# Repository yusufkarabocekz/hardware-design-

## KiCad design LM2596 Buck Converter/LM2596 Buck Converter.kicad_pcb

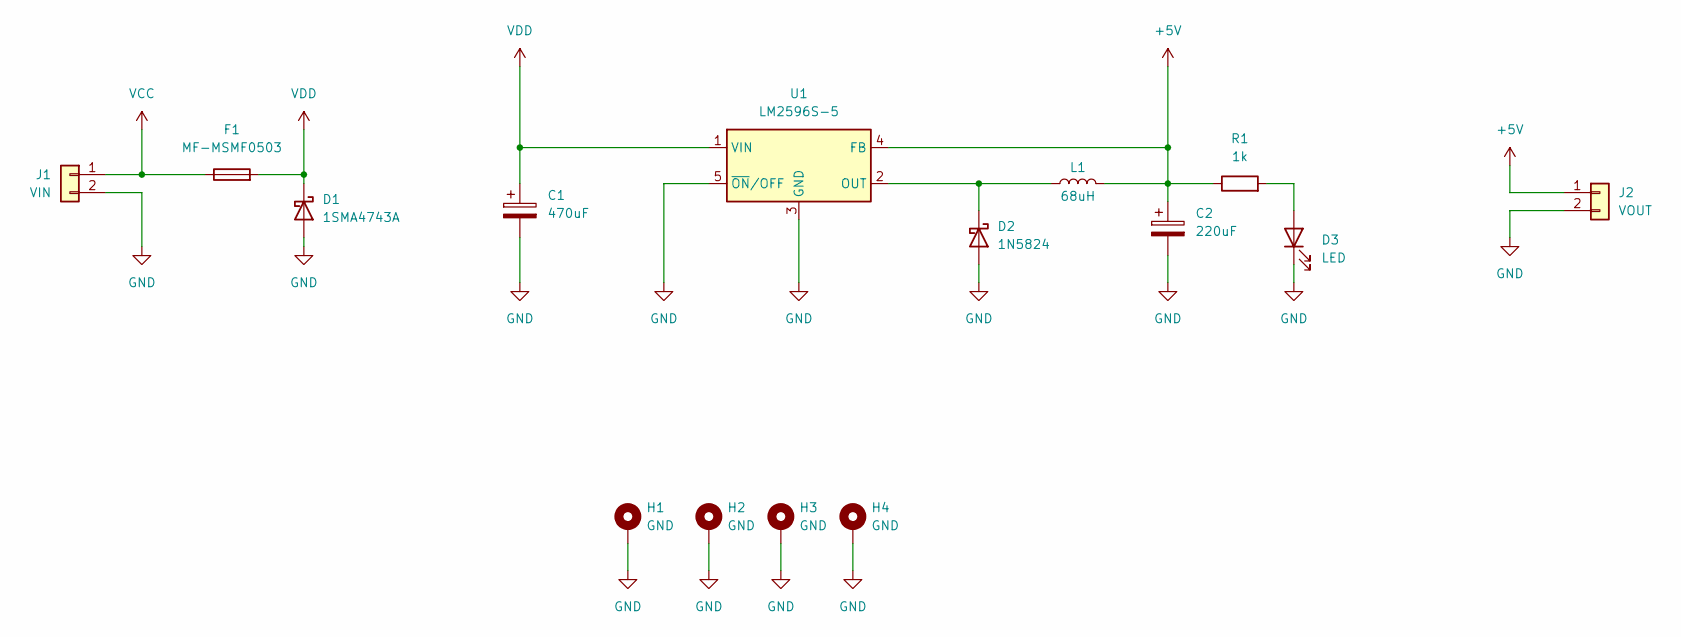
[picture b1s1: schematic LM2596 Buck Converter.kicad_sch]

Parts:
C1: 470uF; CP_Elec_10x10.5
C2: 220uF; CP_Elec_8x10
D1: 1SMA4743A; D_SMA
D2: 1N5824; D_SMC
D3: LED; LED_0805_2012Metric
F1: MF-MSMF0503; Fuse_0603_1608Metric
H1, H2, H3, H4: GND; MountingHole_2.2mm_M2_Pad_Via
J1: VIN; TerminalBlock_Phoenix_MKDS-1,5-2-5.08_1x02_P5.08mm_Horizont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
J2: VOUT; TerminalBlock_Phoenix_MKDS-1,5-2-5.08_1x02_P5.08mm_Horizont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
L1: 68uH; L_Sunlord_MWSA1005S
R1: 1k; R_0805_2012Metric
U1: LM2596S-5; TO-263-5_TabPin3

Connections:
+5V: C2.1, J2.1, L1.2, R1.1, U1.4 (FB)
GND: C1.2, C2.2, D1.2 (A), D2.2 (A), D3.1 (K), H1.1, H2.1, H3.1, H4.1, J1.2, J2.2, U1.3 (GND), U1.5 (~ON/OFF)
unnamed: D2.1 (K), L1.1, U1.2 (OUT)
unnamed: D3.2 (A), R1.2
VCC: F1.1, J1.1
VDD: C1.1, D1.1 (K), F1.2, U1.1 (VIN)

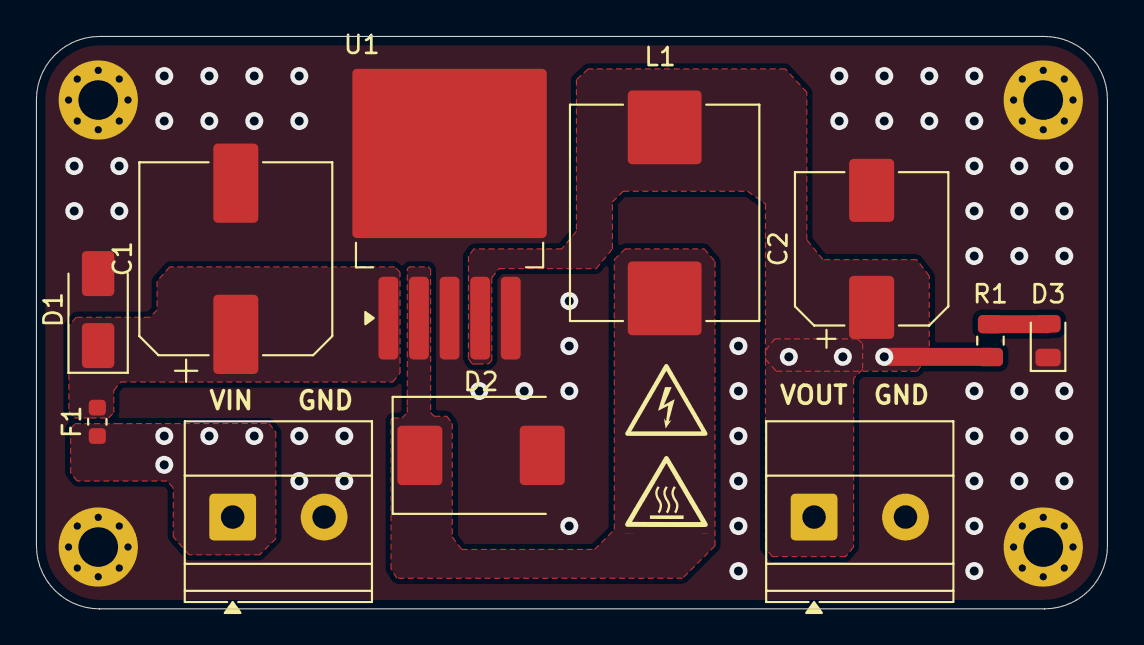
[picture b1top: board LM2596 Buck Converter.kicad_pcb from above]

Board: 2 copper layers, 59.5 x 31.8 mm, 15 parts (0 on the bottom side), 6 nets.

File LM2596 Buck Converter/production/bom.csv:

Designator,Footprint,Quantity,Value,LCSC Part #
C1,CP_Elec_10x10.5,1,470uF,
C2,CP_Elec_8x10,1,220uF,
D1,D_SMA,1,1SMA4743A,
D2,D_SMC,1,1N5824,
D3,0805,1,LED,
F1,0603,1,MF-MSMF0503,
J1,"TerminalBlock_Phoenix_MKDS-1,5-2-5.08_1x02_P5.08mm_Horizontal",1,VIN,
J2,"TerminalBlock_Phoenix_MKDS-1,5-2-5.08_1x02_P5.08mm_Horizontal",1,VOUT,
L1,L_Sunlord_MWSA1005S,1,68uH,
R1,0805,1,1k,
U1,TO-263-5_TabPin3,1,LM2596S-5,

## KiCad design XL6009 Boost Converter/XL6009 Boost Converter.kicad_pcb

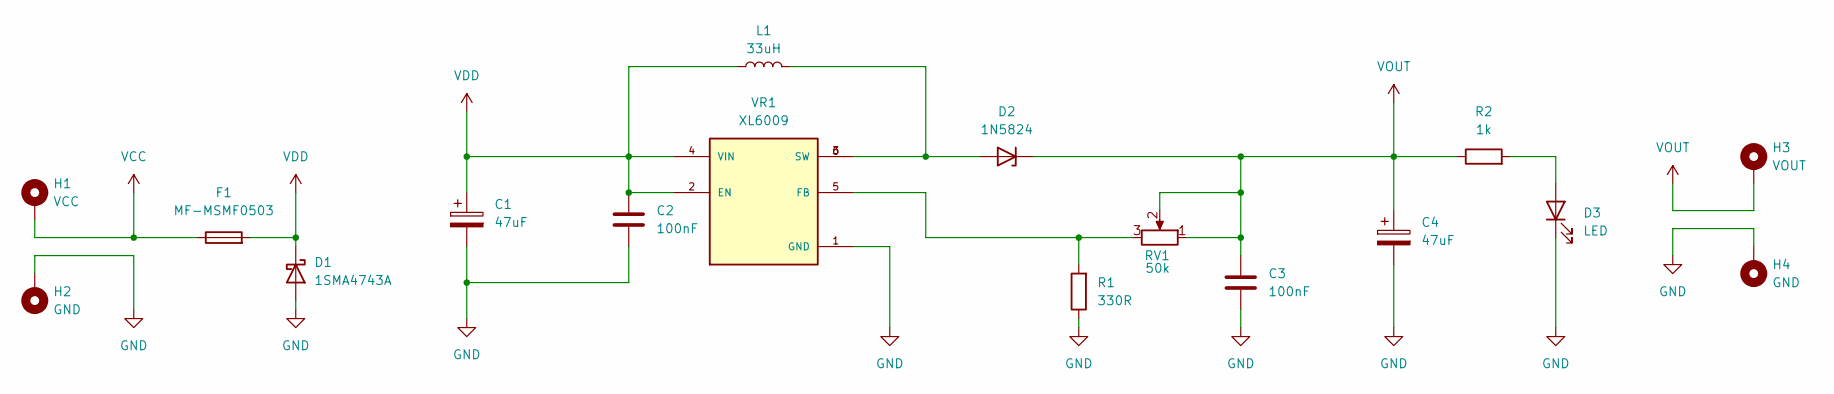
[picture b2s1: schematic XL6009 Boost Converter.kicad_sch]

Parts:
C1: 47uF; CP_Elec_6.3x5.4
C2, C3: 100nF; C_0603_1608Metric
C4: 47uF; CP_Elec_10x10
D1: 1SMA4743A; D_SMA
D2: 1N5824; D_SMA
D3: LED; LED_0805_2012Metric
F1: MF-MSMF0503; Fuse_0603_1608Metric
H1: VCC; MountingHole_2.2mm_M2_Pad_Via
H2, H4: GND; MountingHole_2.2mm_M2_Pad_Via
H3: VOUT; MountingHole_2.2mm_M2_Pad_Via
L1: 33uH; L_Bourns_SRP1050WA
R1: 330R; R_0603_1608Metric
R2: 1k; R_0805_2012Metric
RV1: 50k; Potentiometer_Bourns_3296W_Vertical
VR1: XL6009; DPAK170P1435X465-6N; PARTREV 1.1

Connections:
GND: C1.2, C2.2, C3.2, C4.2, D1.2 (A), D3.1 (K), H2.1, H4.1, R1.1, VR1.1 (GND)
unnamed: D2.2 (A), L1.2, VR1.3 (SW), VR1.6 (SW)
unnamed: D3.2 (A), R2.2
unnamed: R1.2, RV1.3, VR1.5 (FB)
VCC: F1.1, H1.1
VDD: C1.1, C2.1, D1.1 (K), F1.2, L1.1, VR1.2 (EN), VR1.4 (VIN)
VOUT: C3.1, C4.1, D2.1 (K), H3.1, R2.1, RV1.1, RV1.2

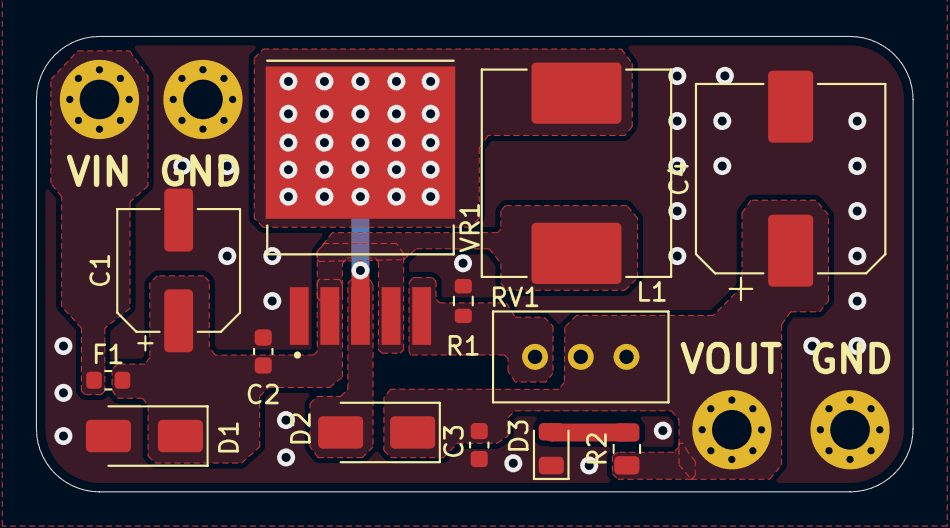
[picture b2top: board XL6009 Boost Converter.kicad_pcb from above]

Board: 2 copper layers, 48.7 x 25.3 mm, 17 parts (0 on the bottom side), 7 nets.

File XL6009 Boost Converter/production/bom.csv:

Designator,Footprint,Quantity,Value,LCSC Part #
C1,CP_Elec_6.3x5.4,1,47uF,
"C2, C3",0603,2,100nF,
C4,CP_Elec_10x10,1,47uF,
D1,D_SMA,1,1SMA4743A,
D2,D_SMA,1,1N5824,
D3,0805,1,LED,
F1,0603,1,MF-MSMF0503,
L1,L_Bourns_SRP1050WA,1,33uH,
R1,0603,1,330R,
R2,0805,1,1k,
RV1,Potentiometer_Bourns_3296W_Vertical,1,50k,
VR1,DPAK170P1435X465-6N,1,XL6009,
